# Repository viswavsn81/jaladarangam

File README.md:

# Mindfulness Instrument

A Raspberry Pi 3 project that plays an instrument sample when a sensor is triggered.
Started as a keyboard-spacebar proof of concept (evdev + pygame); the wiring below is
for the real sensor hardware: 8 FSR402 force sensors, one per note key (Sa through
upper Sa), read through an MCP3008 ADC over SPI. An earlier hardware iteration used
2 FSRs plus a SparkFun SoftPot ribbon for continuous glide; that layout was replaced
by the 8 discrete note keys below, and the SoftPot has since been removed entirely.

The project's original design called for two MCP3008 chips sharing one SPI0 bus
(distinguished by chip-select line): **ADC1** for the 8 note-key FSRs, and **ADC2**
for the gamakam/octave-up/octave-down control keys. ADC1 is documented and wired
below and is the only MCP3008 in the current build. **ADC2 was built, found to
have an unresolved hardware fault, and has been fully replaced** by an Arduino
Nano 33 BLE reading the three control keys directly over USB serial — see
[STATUS.md](STATUS.md) for the current project state and [ADC2 (control keys)](#adc2--control-keys)
below for the (now superseded) ADC2 wiring record.

## Hardware

- Raspberry Pi 3 Model B
- 2x MCP3008 8-channel 10-bit ADC (16-pin DIP, SPI interface) — ADC1 (note keys,
  wired) and ADC2 (control keys, being wired)
- 8x FSR402 round force sensor (18mm) — ADC1's discrete note keys, CH0-CH7 =
  Sa, Ri, Ga, Ma, Pa, Da, Ni, Sa' (upper Sa)
- Resistors: 8x 10kΩ (ADC1, one per note-key FSR) — plus 1x 10kΩ per ADC2
  control-key FSR as those get populated
- Breadboard + jumper wires

## Wiring

All physical pin numbers below refer to the Raspberry Pi's 40-pin GPIO header, and were
verified against the official Raspberry Pi pinout and the Microchip MCP3008 datasheet
(DS20001295E) before wiring.

### Pi -> MCP3008 (ADC1)

| Pi physical pin | Signal | MCP3008 pin |
|---|---|---|
| 1 | 3.3V | 16 (VDD) |
| 1 | 3.3V | 15 (VREF) |
| 6 | GND | 14 (AGND) |
| 6 | GND | 9 (DGND) |
| 23 | GPIO11 / SPI0 SCLK | 13 (CLK) |
| 19 | GPIO10 / SPI0 MOSI | 11 (DIN) |
| 21 | GPIO9 / SPI0 MISO | 12 (DOUT) |
| 24 | GPIO8 / SPI0 CE0 | 10 (CS/SHDN) |

MCP3008 pin 1 (CH0) is at the end of the chip marked with a notch/dot — make sure that
end is oriented correctly on the breadboard before inserting.

### Note-key channel assignment (ADC1)

| MCP3008 pin (channel) | Note key |
|---|---|
| 1 (CH0) | Sa |
| 2 (CH1) | Ri |
| 3 (CH2) | Ga |
| 4 (CH3) | Ma |
| 5 (CH4) | Pa |
| 6 (CH5) | Da |
| 7 (CH6) | Ni |
| 8 (CH7) | Sa' (upper Sa) |

All 8 are discrete FSR keys, matching `jaladarangam.py`'s `LIVE_POSITIONS =
set(range(8))`. There is no SoftPot or continuous-glide sensor in the current
hardware — an earlier prototype iteration used a SoftPot ribbon on CH2 for
continuous pitch glide, but that approach was replaced by these 8 discrete FSR
keys and the SoftPot has been physically removed.

### Sensors (voltage dividers into ADC1)

Identical divider pattern for all 8 note-key FSRs:

| Component | Leg/end | Connects to |
|---|---|---|
| Note-key FSR | leg A | 3.3V rail |
| Note-key FSR | leg B | ADC1 channel pin (per the table above) **and** 10kΩ resistor -> GND |

The 10kΩ resistor forms a voltage divider: FSR resistance drops under pressure,
so the sense-node voltage *rises* with force.

## Step-by-step wiring order (ADC1)

1. Power off / unplug the Pi before wiring anything.
2. Seat the MCP3008 across the breadboard's center gap, pin 1 (notch end) toward CH0.
3. Run the 3.3V rail and GND rail down the breadboard from the Pi's pin 1 and pin 6.
4. Wire MCP3008 VDD (16) and VREF (15) to the 3.3V rail; AGND (14) and DGND (9) to the GND rail.
5. Wire the SPI lines: Pi pin 23 -> MCP3008 CLK (13), Pi pin 19 -> DIN (11),
   Pi pin 21 -> DOUT (12), Pi pin 24 -> CS/SHDN (10).
6. Wire each of the 8 note-key FSRs (Sa through Sa', MCP3008 channels CH0-CH7 per
   the channel-assignment table above): one leg to the 3.3V rail, the other leg to
   its assigned MCP3008 channel pin and to one leg of a 10kΩ resistor whose other
   leg goes to the GND rail. Repeat for all 8 keys.
7. Double-check every connection against the tables above before powering the Pi back on.
8. Once wired, enable SPI on the Pi (`sudo raspi-config nonint do_spi 0`) if not already
   enabled, then reboot before trying to read the MCP3008.

## ADC2 (control keys) — SUPERSEDED, kept for historical/wiring reference only

**This entire section describes an abandoned hardware path.** ADC2 was
physically wired per the plan below, then extensively fault-tested (FSR
swaps, pulldown/ground checks, chip-select swaps, physical chip swaps) after
every channel — including one never wired to anything — read an identical
fixed value no matter what changed. That combination of tests pointed at the
MCP3008 chip/circuit itself, not the wiring, so ADC2 was retired rather than
debugged further. **The three control keys (gamakam, octave+, octave-) are
now read by an Arduino Nano 33 BLE over USB serial instead** — see
[STATUS.md](STATUS.md) and `control_keys/control_keys.ino`. No code in this
repo reads ADC2/CE1. The wiring plan below is left intact only as a record
of what was built and why it didn't work, in case the physical MCP3008/
breadboard setup is ever revisited.

ADC2 is a second MCP3008 sharing the same SPI0 bus as ADC1 (same CLK/DIN/DOUT,
same power/ground rails), distinguished by its own hardware chip-select line
(CE1 instead of ADC1's CE0). It carries the three control keys — gamakam,
octave+, octave- — reserved from the original two-chip instrument design.

### Shared bus (Pi -> ADC2)

Identical to ADC1's bus wiring above — these four signals are shared by both
chips; do not re-run separate jumpers from the Pi for these, just tie ADC2's
matching pins onto the same rails/lines ADC1 already uses.

| Pi physical pin | Signal | MCP3008 pin |
|---|---|---|
| 1 | 3.3V | 16 (VDD) |
| 1 | 3.3V | 15 (VREF) |
| 6 | GND | 14 (AGND) |
| 6 | GND | 9 (DGND) |
| 23 | GPIO11 / SPI0 SCLK | 13 (CLK) |
| 19 | GPIO10 / SPI0 MOSI | 11 (DIN) |
| 21 | GPIO9 / SPI0 MISO | 12 (DOUT) |

### ADC2-specific: chip select

| Pi physical pin | Signal | MCP3008 pin |
|---|---|---|
| 26 | GPIO7 / SPI0 CE1 | 10 (CS/SHDN) |

This is distinct from ADC1's chip-select (Pi physical pin 24, GPIO8 / SPI0 CE0)
— CE0 and CE1 are separate hardware-controlled pins, so make sure ADC2's
CS/SHDN goes to physical pin 26 (GPIO7/CE1), not physical pin 24 (GPIO8/CE0),
which is already committed to ADC1.

### Channel assignment (reserved from the original design)

| MCP3008 pin (channel) | Control key | Status |
|---|---|---|
| 1 (CH0) | gamakam | unpopulated — currently a keyboard-spacebar stand-in in software |
| 2 (CH1) | octave+ | unpopulated |
| 3 (CH2) | octave- | unpopulated |
| 4-8 (CH3-CH7) | spare/unused | reserved for future use, not currently assigned |

### Sensors (voltage dividers into ADC2) — apply per channel as each FSR is added

Same pattern as ADC1's note-key FSRs: for whichever of the three control
channels above has an FSR physically attached, wire it as follows. Do **not**
wire a channel this way until an FSR is actually being installed on it —
until then, leave that channel's row in the table above as "unpopulated."

| Component | Leg/end | Connects to |
|---|---|---|
| Control-key FSR | leg A | 3.3V rail |
| Control-key FSR | leg B | ADC2 channel pin (CH0/CH1/CH2 per the table above) **and** 10kΩ resistor -> GND |

### Step-by-step wiring order (ADC2)

1. Power off / unplug the Pi before wiring anything.
2. Seat the second MCP3008 on the breadboard, pin 1 (notch end) toward CH0, same
   orientation convention as ADC1.
3. Tie ADC2's VDD (16) and VREF (15) onto the existing 3.3V rail; AGND (14) and
   DGND (9) onto the existing GND rail (the same rails ADC1 already uses).
4. Tie ADC2's CLK (13), DIN (11), and DOUT (12) onto the same SPI0 SCLK/MOSI/MISO
   lines ADC1 already uses (Pi physical pins 23/19/21) — these lines are shared,
   not duplicated.
5. Wire ADC2's CS/SHDN (10) to Pi physical pin 26 (GPIO7 / SPI0 CE1) — a new,
   ADC2-only line, separate from ADC1's CE0 on physical pin 24.
6. For each control-key FSR you are physically installing now, wire it per the
   voltage-divider table above into its assigned channel; leave any channel with
   no FSR yet unpopulated rather than wiring a dangling divider.
7. Double-check every connection against the tables above before powering the Pi
   back on, and update the status line at the top of this section to reflect
   exactly which channels are now populated.
8. SPI0 is already enabled from the ADC1 setup; no additional `raspi-config`
   step is needed for a second chip on the same bus.

## Software

- `spacebar_instrument.py` — the keyboard-spacebar proof of concept (evdev + pygame),
  kept as a reference/fallback trigger while the sensor wiring above is being built out.
- `samples/guitar_note.wav` — CC0 guitar sample from OpenGameArt.org
  (https://opengameart.org/content/guitar-0), used by the spacebar PoC.
- `read_fsr_raw.py` — prints raw MCP3008 readings for a channel; used to verify a
  sensor's wiring/divider orientation before building anything on top of it.
- `fsr_oscillator.py` — maps FSR1 (CH0) and FSR2 (CH1) each to a persistent sine
  oscillator (pygame.mixer, 48000Hz/1024-sample buffer) whose pitch tracks pressure;
  an interface-level proof of concept, not the final instrument sound.
- `gamaka.py` — the pressure-controlled pitch-bend (gamaka) proof of concept. FSR1
  triggers/bends a D3 guitar pluck, FSR2 triggers/bends a G3 pluck. Samples are
  streamed through a `sounddevice` callback with a variable-rate linear-interpolation
  reader per voice (pygame.mixer can't vary playback speed live, hence the different
  library here vs. the oscillator above). Raw ADC is EMA-smoothed before driving the
  bend; a fresh pluck triggers on the raw touch-threshold crossing, and the bend
  (0 to +40 cents, `rate = 2^(cents/1200)`) tracks the smoothed value continuously,
  including after release, so pitch settles back down instead of snapping.
- `prepare_samples.py` — one-time preprocessing script that derived `d3_pluck.wav`
  and `g3_pluck.wav` from the source samples below.
- `samples/d3_pluck.wav`, `samples/g3_pluck.wav` — derived from
  [`karoryfer.shinyguitar`](https://github.com/sfzinstruments/karoryfer.shinyguitar)
  (CC0 1.0, verified directly against the repo's `LICENSE` file). That library samples
  in whole tones rather than every semitone, so D3 and G3 aren't recorded directly —
  they're derived from the nearest neighbors (Eb3 and Gb3) via a 1-semitone pitch
  shift, resampled to 48000Hz to match this Pi's PipeWire audio graph quantum.
- `jaladarangam.py` — the current real hardware-driven instrument. Reads all 8
  physical note-key FSRs on ADC1 (CH0-CH7 = Sa..Sa'), with raga-selectable
  positional layout (`--raga`), polyphony (up to 8 notes ringing
  independently), mandolin/guitar/flute instrument switching with
  per-instrument envelopes (flute stops promptly on release; mandolin/guitar
  ring through their natural decay), octave-aware jaru (glide) and octave-
  nearest note selection, gamakam/octave+/octave- read from an Arduino Nano
  33 BLE over USB serial (see `control_keys/control_keys.ino`), odukkal
  (pressure-to-pitch-bend, toggleable), attack velocity, the double bass
  drone, a live 3-band EQ, master volume, and dual I2S+headphone output. All
  of the above is controllable via typed stdin commands, a WiFi WebSocket
  server (port 8765), and a Bluetooth Classic SPP connection (no PIN
  pairing) — all three dispatch through the same command layer, both
  network transports run persistently via systemd
  (`systemd/jaladarangam.service`), and both are documented in full in
  **[PROTOCOL.md](PROTOCOL.md)** (the contract for building a remote-control
  app against). Known limitation: a tanpura drone was scoped
  but is **not implemented** (no CC0/permissive-license sample could be
  sourced that was also actually downloadable — a Freesound recording was
  gated behind account login, and a Pixabay mirror of it was blocked by
  Cloudflare bot-protection from this environment's tools). Usage:
  `python3 jaladarangam.py --raga Shankarabharanam`.

### Control-key software support (superseded — now via Arduino Nano, not ADC2)

`jaladarangam.py` reads only ADC1 (CE0) for note keys — no code in this repo
opens or reads ADC2 (CE1) at all, since ADC2 was retired (see above). The
gamakam/octave+/octave- control keys are real hardware today, but read from
an Arduino Nano 33 BLE over USB serial (`poll_nano_values`), not from ADC2 or
any keyboard stand-in. See [STATUS.md](STATUS.md) for the current summary and
`control_keys/control_keys.ino` for the Nano's own firmware.

`gamaka.py`, `read_fsr_raw.py`, and `fsr_oscillator.py` each open a single
spidev bus (ADC1/CE0 only) with no CE1/ADC2 handling, and are unrelated to
`jaladarangam.py`'s Nano integration. The keyboard-based prototypes
(`sliding_window_raga.py`, `gamaka_keyboard.py`, `gamaka_keyboard_mixer.py`)
stand in for control keys with keyboard input (e.g. spacebar for gamakam,
bracket keys for octave up/down) and don't touch spidev at all — these are
separate, earlier scripts, left unchanged.

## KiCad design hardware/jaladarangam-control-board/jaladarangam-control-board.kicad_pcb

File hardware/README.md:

# Jaladarangam Instrument Control Board

KiCad 10 project for the instrument's control board: a Raspberry Pi 3 reads 8
analog FSR note keys through an MCP3008 SPI ADC, and drives 8 vibration motors
through a 74HC595 shift register feeding a ULN2803A Darlington array. A 74HC165
is fitted as a socketed but unpopulated digital-input expansion.

Logic runs at 3.3 V. **MOTOR_V+ is a separate supply rail** sharing only GND
with the logic domain — it is never tied to +3V3.

Board: 145 × 110 mm, 2 layers, through-hole throughout, all four ICs socketed.

## Everything is generated from one file

`scripts/board_spec.py` is the single source of truth: components, pin-to-net
assignments, schematic and PCB placement, design rules and net classes. The
schematic, PCB, project file and BOM are all generated from it, so there is no
second place for the wiring to drift.

Nothing here is hand-edited. To change the board, change `board_spec.py` and
re-run the pipeline.

```
scripts/build.sh     board_spec -> .kicad_pro -> .kicad_sch -> .kicad_pcb -> .dsn
scripts/route.sh     autoroute, import the session, DRC, zone check
scripts/fab.sh       gerbers, drill files, BOM
scripts/make_review.sh   3D renders, 2D layout, silkscreen close-ups -> review/
```

The order in `build.sh` matters. `make_project_file.py` writes the net classes
into the `.kicad_pro`; `gen_pcb.py` then **binds that project to the board**
before saving. A bare `pcbnew.BOARD()` carries KiCad's built-in defaults (one
0.2 mm class), and saving such a board writes those defaults straight over the
project file — which is exactly how the MOTOR_V+ Power class was silently lost
once. `gen_pcb.py` now refuses to write a board whose net classes are wrong.

## Verification

Each stage is checked independently rather than trusted:

| Check | What it proves |
|---|---|
| `board_spec.sanity_check` | No duplicate refs, no single-pad nets, MOTOR_V+ and +3V3 share no pad, divider/driver/aux nets have the right pad counts, every polarity mark agrees with the net on its pad |
| `verify_polarity.py` | Every silkscreen polarity mark sits nearest the pad it names, and that pad carries the net the mark asserts |
| `kicad-cli sch erc` | KiCad's own electrical rules — 0 violations |
| `verify_netlist.py` | KiCad's exported netlist matches `board_spec` pad-for-pad, and every deliberately open pin is accounted for |
| `verify_netclasses.py` | The DSN handed to the router really carries 0.8 mm on the motor rail and 0.4 mm on signals |
| `import_ses.py` | Track widths that actually landed on copper match their net class |
| `kicad-cli pcb drc` | 0 violations, 0 unconnected |
| `verify_zones.py` | Motor and analog copper stayed in their own zones after routing |

## Review images

`review/` is the single home for reviewable output - schematic and board, PDF
and PNG - so the design can be looked at without opening KiCad. It regenerates
with `scripts/make_review.sh`:

| File | What it shows |
|---|---|
| `schematic.pdf` | Full schematic, vector - the one to read properly |
| `schematic.png` | Same sheet at 300 dpi, for a quick look |
| `pcb_routed.pdf` | Routed board, vector |
| `pcb_3d_iso.png` | 3D isometric with component bodies |
| `pcb_3d_top.png` / `pcb_3d_bottom.png` | 3D straight-on, both sides |
| `pcb_2d_layout.png` | 2D layout: both copper layers, silkscreen, outline |
| `pcb_silkscreen.png` | Silkscreen + board outline only, no copper |
| `silk_fsr_headers.png` | Close-up: FSR note-key headers J2-J9 |
| `silk_motor_headers.png` | Close-up: motor headers J10-J17 |
| `silk_motor_power.png` | Close-up: motor supply input J18 |
| `silk_aux_header.png` | Close-up: AUX digital input header J19 |
| `silk_pi_header.png` | Close-up: Raspberry Pi GPIO header J1 |

The silkscreen views plot `F.Silkscreen` and `Edge.Cuts` only, in black and
white - no copper behind the captions, and far better contrast than KiCad's
silkscreen yellow on a white page. `Edge.Cuts` is kept purely for orientation.

Crops come from the footprints themselves (`dump_regions.py` reads the board),
not hard-coded rectangles, so they stay correct if placement changes. KiCad's
`--page-size-mode 2` SVG carries a viewBox in board millimetres, so a crop is
just a narrowed viewBox rather than pixel arithmetic.

The schematic is one A2 sheet. PDF is the primary form because it stays vector
and a dense sheet reads at any zoom; the 300 dpi PNG is there for convenience.
The PNG step is driven by the PDF's actual page count, so extra sheets would be
exported as `schematic_p1.png`, `schematic_p2.png` rather than silently lost.

3D renders need the 3D model packages, which the lite AppImage omits;
`kienv.sh` points `KICAD10_3DMODEL_DIR` at a full KiCad extract when one is
present and warns if it is not. U4 renders as bare pads because KiCad hides
3D models for DNP parts - its socket is still fitted.

## Toolchain

No root, no paid services.

- **KiCad 10.0.6**, official AppImage in `/home/pyru/opt/kicad10`. Provides
  `kicad-cli` and a bundled `python3.11` with `pcbnew`.
- **FreeRouting 2.4.1** headless CLI in `/home/pyru/opt/freerouting`, via a
  Specctra DSN → SES round-trip.
- **Temurin JDK 25** in `/home/pyru/opt/jdk25` — FreeRouting's jar is
  class-file 69 and the system JDK is 21.

`scripts/kienv.sh` wires these together and keeps KiCad's config and library
tables inside `hardware/.kicad-config/`, so builds do not depend on any
developer's `~/.config/kicad` state.

## Layout

Signal flow runs left to right, with the two noisy domains held apart:

```
Pi header | analog input zone | << 14 mm empty corridor >> | motor driver zone
(left edge) (FSR headers top    (nothing routed across it   (motor headers
             edge, pulldowns,     but GND and +3V3)          right edge,
             MCP3008)                                        supply bottom)
                 |
   74HC165 expansion block (DNP) along the bottom edge
```

Every off-board connector is edge-accessible and captioned on silkscreen:
`FSR0-7`, `M0-7`, `MOTOR PWR`, `GND AUX D0-D7 GND`, `RPi GPIO`.

## Notes for assembly

- Fit all four IC sockets, **including U4's** — the 74HC165 itself is the only
  DNP part, so the expansion can be populated later with no rework. Its
  pulldowns (R9-R16) and header (J19) are populated.
- J19 is a 1×10: pins 1 and 10 are GND, pins 2-9 are D0-D7.
- Each FSR header is `+3V3` on pin 1, channel node on pin 2. The 10 k pulldown
  is on-board; the FSR forms the upper leg of the divider.
- Each motor header is `MOTOR_V+` on pin 1 (marked `+`), the ULN2803A output
  on pin 2 (marked `-`). Pin 1 is the rectangular pad, with the L-shaped silk
  corner beside it. Wire the motor's positive lead to `+`.
- J18 is marked `+` (MOTOR_V+) and `GND`. Getting it backwards would put the
  motor rail onto the board's ground net.
- `fab/bom.csv` includes the sockets and the off-board parts;
  `fab/bom_kicad.csv` is KiCad's own export of the schematic parts only.

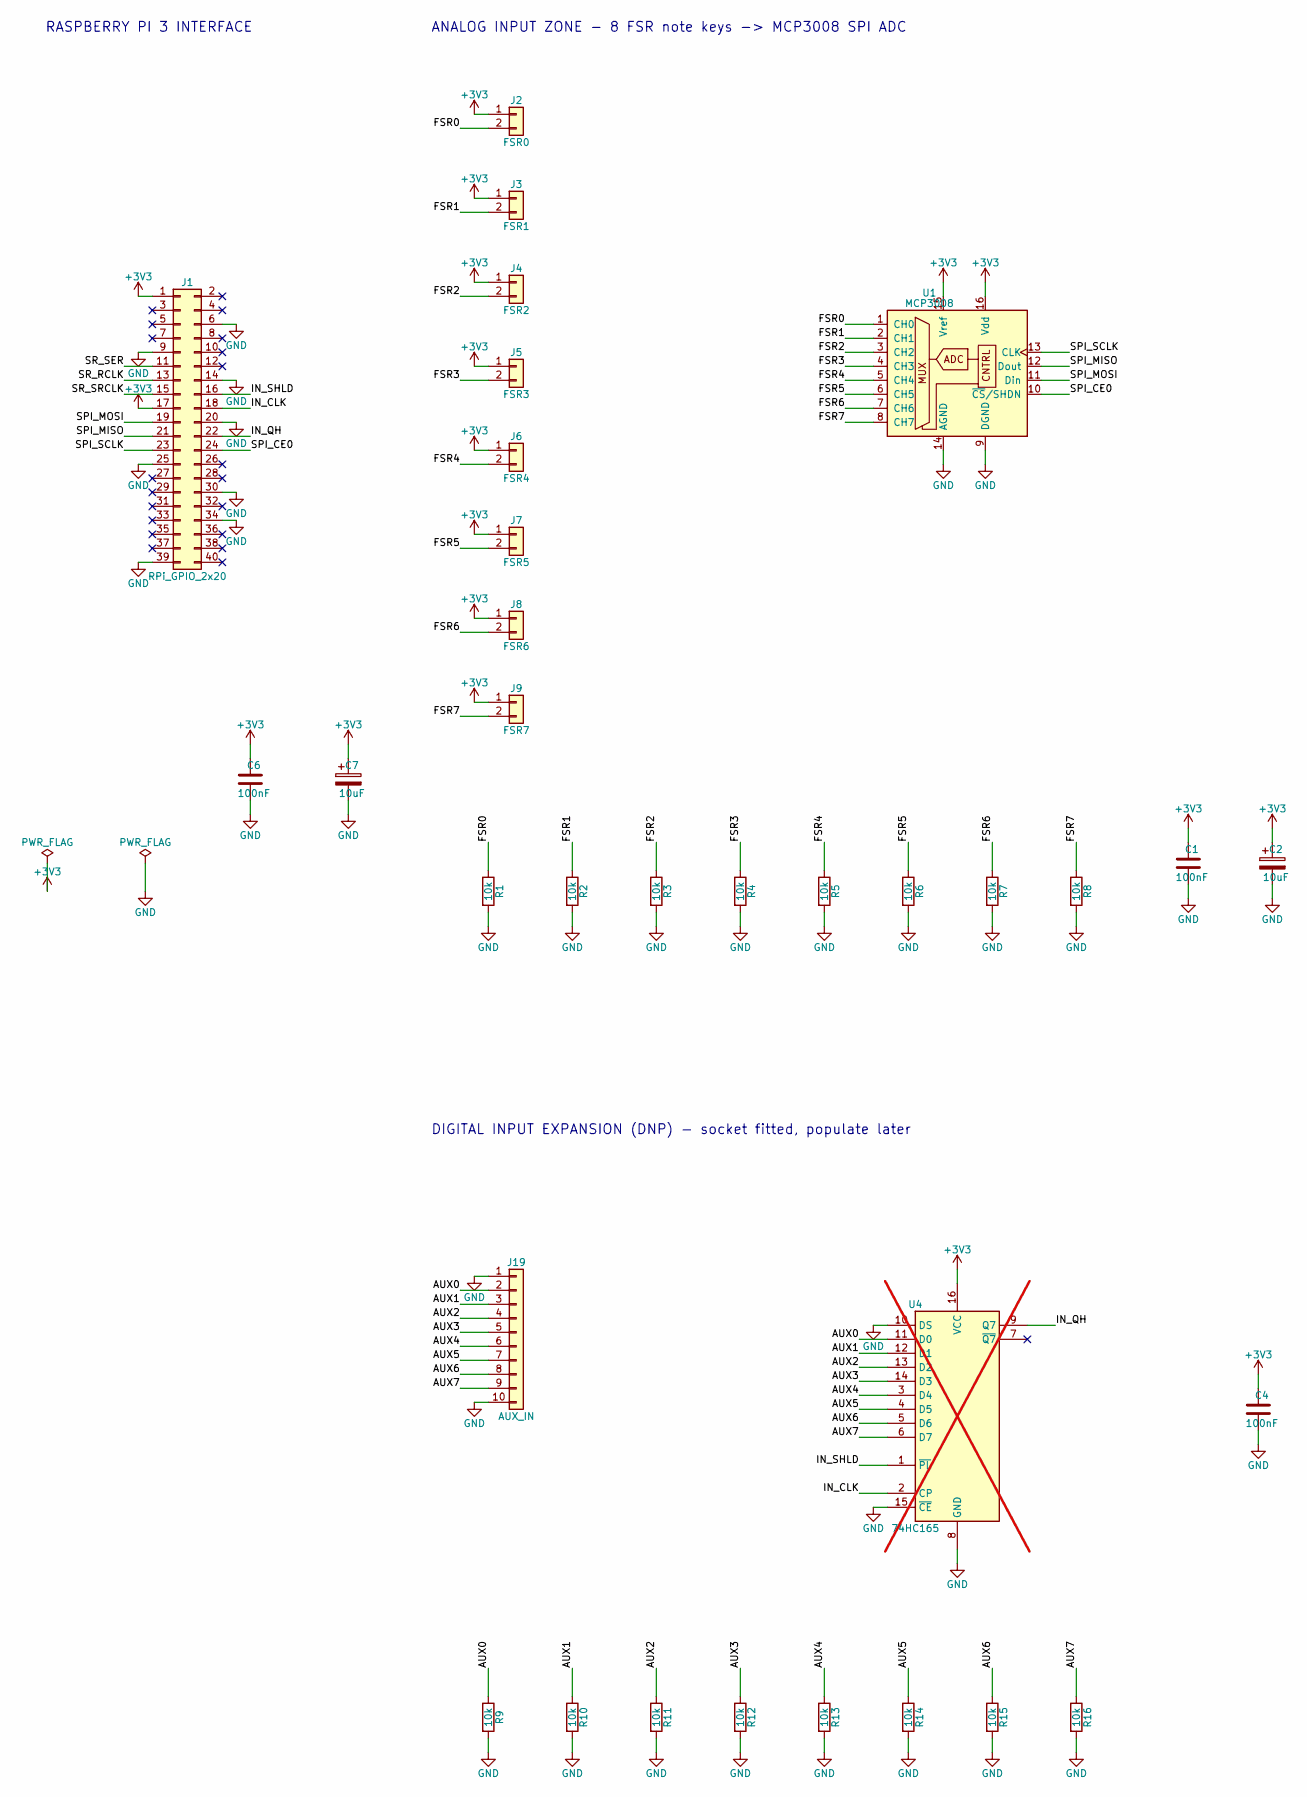
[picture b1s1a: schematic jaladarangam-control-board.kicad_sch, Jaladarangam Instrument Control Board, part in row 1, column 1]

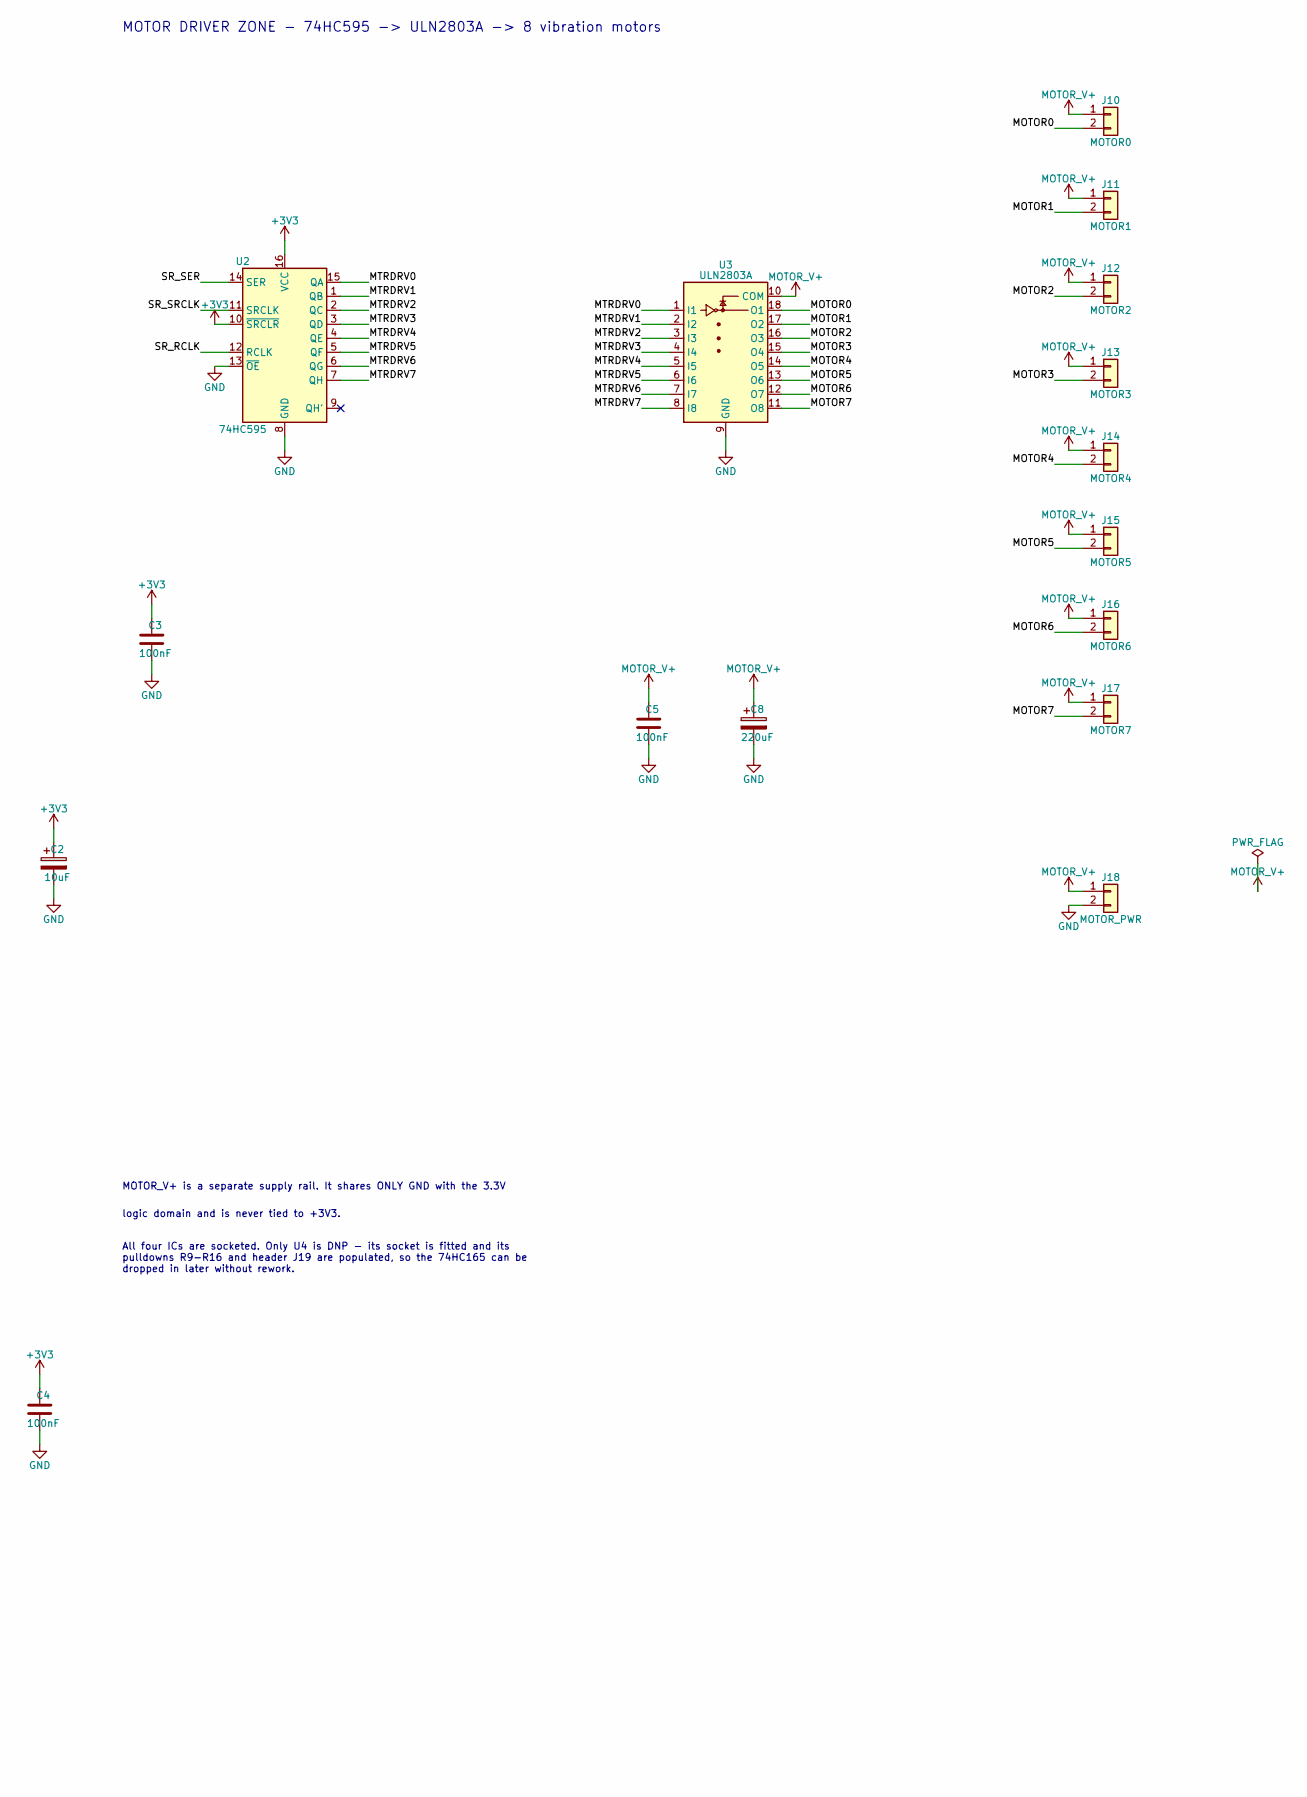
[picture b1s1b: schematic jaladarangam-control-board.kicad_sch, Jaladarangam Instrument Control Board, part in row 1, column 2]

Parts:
C1, C3, C4, C5, C6: 100nF; C_Disc_D5.0mm_W2.5mm_P5.00mm
C2, C7: 10uF; CP_Radial_D5.0mm_P2.50mm
C8: 220uF; CP_Radial_D8.0mm_P3.50mm
J1: RPi_GPIO_2x20; PinHeader_2x20_P2.54mm_Vertical
J2: FSR0; PinHeader_1x02_P2.54mm_Vertical
J3: FSR1; PinHeader_1x02_P2.54mm_Vertical
J4: FSR2; PinHeader_1x02_P2.54mm_Vertical
J5: FSR3; PinHeader_1x02_P2.54mm_Vertical
J6: FSR4; PinHeader_1x02_P2.54mm_Vertical
J7: FSR5; PinHeader_1x02_P2.54mm_Vertical
J8: FSR6; PinHeader_1x02_P2.54mm_Vertical
J9: FSR7; PinHeader_1x02_P2.54mm_Vertical
J10: MOTOR0; PinHeader_1x02_P2.54mm_Vertical
J11: MOTOR1; PinHeader_1x02_P2.54mm_Vertical
J12: MOTOR2; PinHeader_1x02_P2.54mm_Vertical
J13: MOTOR3; PinHeader_1x02_P2.54mm_Vertical
J14: MOTOR4; PinHeader_1x02_P2.54mm_Vertical
J15: MOTOR5; PinHeader_1x02_P2.54mm_Vertical
J16: MOTOR6; PinHeader_1x02_P2.54mm_Vertical
J17: MOTOR7; PinHeader_1x02_P2.54mm_Vertical
J18: MOTOR_PWR; TerminalBlock_MaiXu_MX126-5.0-02P_1x02_P5.00mm
J19: AUX_IN; PinHeader_1x10_P2.54mm_Vertical
R1, R2, R3, R4, R5, R6, R7, R8, R9, R10, R11, R12, R13, R14, R15, R16: 10k; R_Axial_DIN0207_L6.3mm_D2.5mm_P10.16mm_Horizontal
U1: MCP3008; DIP-16_W7.62mm_Socket
U2: 74HC595; DIP-16_W7.62mm_Socket
U3: ULN2803A; DIP-18_W7.62mm_Socket
U4: 74HC165; DIP-16_W7.62mm_Socket; not fitted

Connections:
+3V3: C1.1, C2.1, C3.1, C4.1, C6.1, C7.1, J1.1, J1.17, J2.1, J3.1, J4.1, J5.1, J6.1, J7.1, J8.1, J9.1, U1.15 (Vref), U1.16 (Vdd), U2.10 (~SRCLR), U2.16 (VCC), U4.16 (VCC)
AUX0: J19.2, R9.1, U4.11 (D0)
AUX1: J19.3, R10.1, U4.12 (D1)
AUX2: J19.4, R11.1, U4.13 (D2)
AUX3: J19.5, R12.1, U4.14 (D3)
AUX4: J19.6, R13.1, U4.3 (D4)
AUX5: J19.7, R14.1, U4.4 (D5)
AUX6: J19.8, R15.1, U4.5 (D6)
AUX7: J19.9, R16.1, U4.6 (D7)
FSR0: J2.2, R1.1, U1.1 (CH0)
FSR1: J3.2, R2.1, U1.2 (CH1)
FSR2: J4.2, R3.1, U1.3 (CH2)
FSR3: J5.2, R4.1, U1.4 (CH3)
FSR4: J6.2, R5.1, U1.5 (CH4)
FSR5: J7.2, R6.1, U1.6 (CH5)
FSR6: J8.2, R7.1, U1.7 (CH6)
FSR7: J9.2, R8.1, U1.8 (CH7)
GND: C1.2, C2.2, C3.2, C4.2, C5.2, C6.2, C7.2, C8.2, J1.6, J1.9, J1.14, J1.20, J1.25, J1.30, J1.34, J1.39, J18.2, J19.1, J19.10, R1.2, R2.2, R3.2, R4.2, R5.2, R6.2, R7.2, R8.2, R9.2, R10.2, R11.2, R12.2, R13.2, R14.2, R15.2, R16.2, U1.9 (DGND), U1.14 (AGND), U2.8 (GND), U2.13 (~OE), U3.9 (GND), U4.8 (GND), U4.10 (DS), U4.15 (~CE)
IN_CLK: J1.18, U4.2 (CP)
IN_QH: J1.22, U4.9 (Q7)
IN_SHLD: J1.16, U4.1 (~PL)
MOTOR0: J10.2, U3.18 (O1)
MOTOR1: J11.2, U3.17 (O2)
MOTOR2: J12.2, U3.16 (O3)
MOTOR3: J13.2, U3.15 (O4)
MOTOR4: J14.2, U3.14 (O5)
MOTOR5: J15.2, U3.13 (O6)
MOTOR6: J16.2, U3.12 (O7)
MOTOR7: J17.2, U3.11 (O8)
MOTOR_V+: C5.1, C8.1, J10.1, J11.1, J12.1, J13.1, J14.1, J15.1, J16.1, J17.1, J18.1, U3.10 (COM)
MTRDRV0: U2.15 (QA), U3.1 (I1)
MTRDRV1: U2.1 (QB), U3.2 (I2)
MTRDRV2: U2.2 (QC), U3.3 (I3)
MTRDRV3: U2.3 (QD), U3.4 (I4)
MTRDRV4: U2.4 (QE), U3.5 (I5)
MTRDRV5: U2.5 (QF), U3.6 (I6)
MTRDRV6: U2.6 (QG), U3.7 (I7)
MTRDRV7: U2.7 (QH), U3.8 (I8)
SPI_CE0: J1.24, U1.10 (~CS/SHDN)
SPI_MISO: J1.21, U1.12 (Dout)
SPI_MOSI: J1.19, U1.11 (Din)
SPI_SCLK: J1.23, U1.13 (CLK)
SR_RCLK: J1.13, U2.12 (RCLK)
SR_SER: J1.11, U2.14 (SER)
SR_SRCLK: J1.15, U2.11 (SRCLK)

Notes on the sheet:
ANALOG INPUT ZONE - 8 FSR note keys -> MCP3008 SPI ADC
MOTOR DRIVER ZONE - 74HC595 -> ULN2803A -> 8 vibration motors
DIGITAL INPUT EXPANSION (DNP) - socket fitted, populate later
RASPBERRY PI 3 INTERFACE
MOTOR_V+ is a separate supply rail. It shares ONLY GND with the 3.3V
logic domain and is never tied to +3V3.
All four ICs are socketed. Only U4 is DNP - its socket is fitted and its pulldowns R9-R16 and header J19 are populated, so the 74HC165 can be dropped in later without rework.

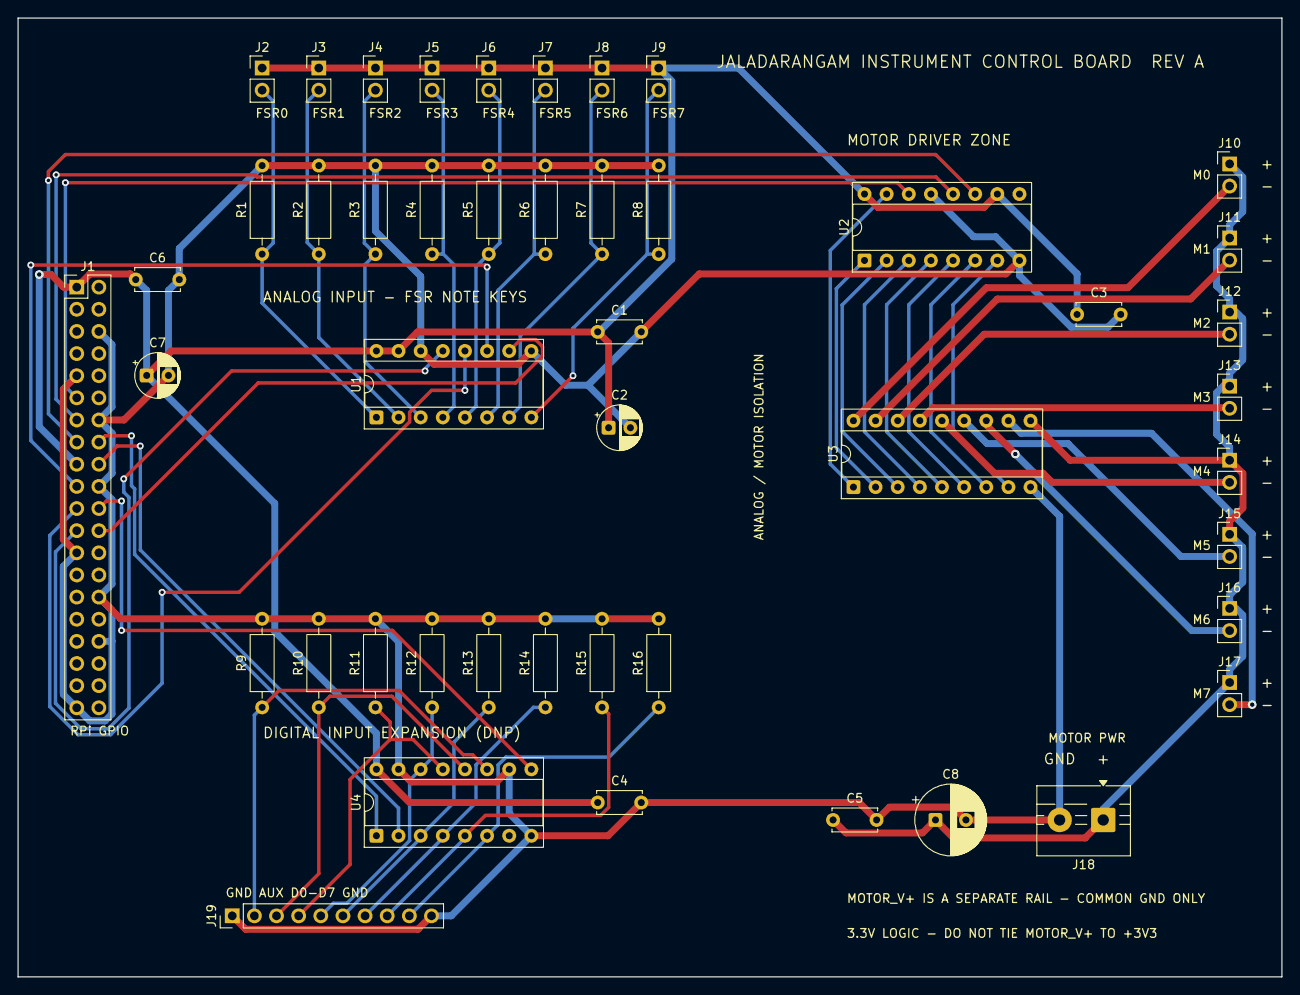
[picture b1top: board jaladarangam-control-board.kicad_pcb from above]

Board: 2 copper layers, 145.0 x 110.0 mm, 47 parts (0 on the bottom side), 45 nets.

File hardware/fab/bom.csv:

Item,Refs,Qty,Value,Footprint,DNP,Notes
Board part,J1,1,RPi_GPIO_2x20,Connector_PinHeader_2.54mm:PinHeader_2x20_P2.54mm_Vertical,,Raspberry Pi 3 40-pin GPIO header
Board part,U1,1,MCP3008,Package_DIP:DIP-16_W7.62mm_Socket,,8-channel 10-bit SPI ADC (socketed)
Board part,"R1,R2,R3,R4,R5,R6,R7,R8,R9,R10,R11,R12,R13,R14,R15,R16",16,10k,Resistor_THT:R_Axial_DIN0207_L6.3mm_D2.5mm_P10.16mm_Horizontal,,"FSR divider pulldown, channel 0"
Board part,J2,1,FSR0,Connector_PinHeader_2.54mm:PinHeader_1x02_P2.54mm_Vertical,,Off-board FSR note key 0
Board part,J3,1,FSR1,Connector_PinHeader_2.54mm:PinHeader_1x02_P2.54mm_Vertical,,Off-board FSR note key 1
Board part,J4,1,FSR2,Connector_PinHeader_2.54mm:PinHeader_1x02_P2.54mm_Vertical,,Off-board FSR note key 2
Board part,J5,1,FSR3,Connector_PinHeader_2.54mm:PinHeader_1x02_P2.54mm_Vertical,,Off-board FSR note key 3
Board part,J6,1,FSR4,Connector_PinHeader_2.54mm:PinHeader_1x02_P2.54mm_Vertical,,Off-board FSR note key 4
Board part,J7,1,FSR5,Connector_PinHeader_2.54mm:PinHeader_1x02_P2.54mm_Vertical,,Off-board FSR note key 5
Board part,J8,1,FSR6,Connector_PinHeader_2.54mm:PinHeader_1x02_P2.54mm_Vertical,,Off-board FSR note key 6
Board part,J9,1,FSR7,Connector_PinHeader_2.54mm:PinHeader_1x02_P2.54mm_Vertical,,Off-board FSR note key 7
Board part,U2,1,74HC595,Package_DIP:DIP-16_W7.62mm_Socket,,8-bit serial-in parallel-out shift register (socketed)
Board part,U3,1,ULN2803A,Package_DIP:DIP-18_W7.62mm_Socket,,8-channel Darlington driver array (socketed)
Board part,J10,1,MOTOR0,Connector_PinHeader_2.54mm:PinHeader_1x02_P2.54mm_Vertical,,Off-board vibration motor 0
Board part,J11,1,MOTOR1,Connector_PinHeader_2.54mm:PinHeader_1x02_P2.54mm_Vertical,,Off-board vibration motor 1
Board part,J12,1,MOTOR2,Connector_PinHeader_2.54mm:PinHeader_1x02_P2.54mm_Vertical,,Off-board vibration motor 2
Board part,J13,1,MOTOR3,Connector_PinHeader_2.54mm:PinHeader_1x02_P2.54mm_Vertical,,Off-board vibration motor 3
Board part,J14,1,MOTOR4,Connector_PinHeader_2.54mm:PinHeader_1x02_P2.54mm_Vertical,,Off-board vibration motor 4
Board part,J15,1,MOTOR5,Connector_PinHeader_2.54mm:PinHeader_1x02_P2.54mm_Vertical,,Off-board vibration motor 5
Board part,J16,1,MOTOR6,Connector_PinHeader_2.54mm:PinHeader_1x02_P2.54mm_Vertical,,Off-board vibration motor 6
Board part,J17,1,MOTOR7,Connector_PinHeader_2.54mm:PinHeader_1x02_P2.54mm_Vertical,,Off-board vibration motor 7
Board part,J18,1,MOTOR_PWR,TerminalBlock:TerminalBlock_MaiXu_MX126-5.0-02P_1x02_P5.00mm,,Separate motor supply input (V+ / GND)
Board part,U4,1,74HC165,Package_DIP:DIP-16_W7.62mm_Socket,DNP,"8-bit parallel-in shift register (socketed, DNP)"
Board part,J19,1,AUX_IN,Connector_PinHeader_2.54mm:PinHeader_1x10_P2.54mm_Vertical,,"Auxiliary digital input header (GND, D0..D7, GND)"
Board part,"C1,C3,C4,C6,C5",5,100nF,Capacitor_THT:C_Disc_D5.0mm_W2.5mm_P5.00mm,,U1 VDD decoupling
Board part,"C2,C7",2,10uF,Capacitor_THT:CP_Radial_D5.0mm_P2.50mm,,MCP3008 VREF/VDD bulk
Board part,C8,1,220uF,Capacitor_THT:CP_Radial_D8.0mm_P3.50mm,,Motor supply bulk reservoir
Socket,"for U1,U2,U4",3,"DIP-16 socket, 7.62mm",Package_DIP:DIP-16_W7.62mm_Socket,,16-pin 0.3in DIP IC socket - fit the socket even where the IC is DNP.
Socket,for U3,1,"DIP-18 socket, 7.62mm",Package_DIP:DIP-18_W7.62mm_Socket,,18-pin 0.3in DIP IC socket - fit the socket even where the IC is DNP.
Off-board,FSR0-FSR7,8,Force-sensing resistor,,,"Note key sensor, wired to J2-J9. Forms the upper leg of each divider against the on-board 10k pulldown."
Off-board,M0-M7,8,Vibration motor,,,"Wired to J10-J17. Positive lead to the header's MOTOR_V+ pin, negative to the ULN2803A output pin."
Off-board,PSU,1,Motor supply,,,"Separate supply into J18, sized for 8 motors. Shares only GND with the 3.3V logic domain."

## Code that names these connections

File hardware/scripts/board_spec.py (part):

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    "17": NET_3V3,         # 3V3 power
    "6": NET_GND, "9": NET_GND, "14": NET_GND, "20": NET_GND,
    "25": NET_GND, "30": NET_GND, "34": NET_GND, "39": NET_GND,
    "11": "SR_SER",        # GPIO17 -> 74HC595 SER
    "13": "SR_RCLK",       # GPIO27 -> 74HC595 RCLK
    "15": "SR_SRCLK",      # GPIO22 -> 74HC595 SRCLK
    "16": "IN_SHLD",       # GPIO23 -> 74HC165 SH/LD
    "18": "IN_CLK",        # GPIO24 -> 74HC165 CLK (separate from SR_SRCLK)
    "19": "SPI_MOSI",      # GPIO10 -> MCP3008 DIN
    "21": "SPI_MISO",      # GPIO9  <- MCP3008 DOUT
    "22": "IN_QH",         # GPIO25 <- 74HC165 QH
    "23": "SPI_SCLK",      # GPIO11 -> MCP3008 CLK
    "24": "SPI_CE0",       # GPIO8  -> MCP3008 CS/SHDN
}

# Pi header pins with no board connection, flagged no-connect so ERC is clean.
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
